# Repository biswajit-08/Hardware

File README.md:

# AC-DC Converter PCB

A custom AC-DC converter circuit and PCB designed using **KiCad**.

This project contains the complete schematic and PCB layout, including component placement, routing, and design files.

> ⚠️ **Safety Warning:** This project may involve hazardous mains voltage. Do not build, modify, test, or operate the circuit unless you understand electrical safety practices and have appropriate isolation, protection, equipment, and supervision.

---

## 📌 Project Overview

The objective of this project is to design a compact and organized PCB for an AC-DC power conversion circuit.

The project covers:

- Circuit schematic design
- Component selection
- PCB layout
- Component placement
- PCB routing
- Design-rule checking
- KiCad project management

---

## 🛠️ Design Software

| Tool | Purpose |
|---|---|
| KiCad | Schematic and PCB design |
| Git | Version control |
| GitHub | Project hosting and collaboration |

---

## 📁 Project Files

```text
AC-DC Converter/
│
├── AC-DC Converter.kicad_pro   # KiCad project
├── AC-DC Converter.kicad_sch   # Schematic
├── AC-DC Converter.kicad_pcb   # PCB layout
└── README.md                   # Project documentation
```

### KiCad Files

**`.kicad_pro`**

Contains the KiCad project configuration.

**`.kicad_sch`**

Contains the complete circuit schematic.

**`.kicad_pcb`**

Contains the PCB layout, including:

- Board outline
- Component footprints
- Component placement
- Copper tracks
- Routing
- PCB layers
- Design rules

---

## ⚡ Electrical Specifications

> Replace the values below with the actual specifications of your design.

| Parameter | Value |
|---|---|
| Input Voltage | TBD |
| Input Frequency | TBD |
| Output Voltage | TBD |
| Output Current | TBD |
| Output Power | TBD |
| Converter Topology | TBD |
| Isolation | TBD |
| PCB Layers | TBD |
| PCB Dimensions | TBD |

---

## 🔌 Functional Block Diagram

```text
        AC INPUT
           │
           ▼
   ┌─────────────────┐
   │ Input Protection│
   └────────┬────────┘
            │
            ▼
   ┌─────────────────┐
   │ Rectification   │
   └────────┬────────┘
            │
            ▼
   ┌─────────────────┐
   │ AC-DC Conversion│
   │ / Switching     │
   └────────┬────────┘
            │
            ▼
   ┌─────────────────┐
   │ Filtering       │
   └────────┬────────┘
            │
            ▼
        DC OUTPUT
```

> Update this block diagram to match the actual topology of your converter.

---

## 🧩 Main Components

The PCB contains the major components required for the converter, including:

- Input protection components
- Rectifier section
- Switching/conversion stage
- Transformer or isolation stage, if applicable
- Filtering components
- Voltage regulation/control circuitry
- Output terminals/connectors

The exact component values and part numbers are available in the KiCad schematic.

---

## 🎨 PCB Design

The PCB was designed with attention to:

- Component placement
- Signal routing
- Power routing
- Ground connections
- Clearance
- Track width
- Thermal considerations
- High-voltage and low-voltage separation

### PCB Design Stages

```text
Schematic
    │
    ▼
Component Selection
    │
    ▼
Footprint Assignment
    │
    ▼
PCB Placement
    │
    ▼
Routing
    │
    ▼
Design Rule Check
    │
    ▼
Fabrication
    │
    ▼
Assembly & Testing
```

---

## 🔍 Design Validation

Before fabrication, the design should be checked for:

- [ ] Electrical Rule Check (ERC)
- [ ] Design Rule Check (DRC)
- [ ] Unconnected nets
- [ ] Clearance violations
- [ ] Track-width requirements
- [ ] Component orientation
- [ ] Polarity of components
- [ ] Connector pinout
- [ ] Thermal requirements
- [ ] High-voltage clearance and creepage

---

## 🏭 Fabrication

Gerber and drill files can be generated from KiCad when the PCB is ready for manufacturing.

Recommended fabrication outputs:

```text
Fabrication/
├── Gerber files
├── Drill files
├── Board outline
├── Copper layers
├── Solder mask
├── Silkscreen
└── Fabrication drawings
```

---

## 🧪 Testing Plan

After fabrication and assembly, testing should be performed progressively.

### 1. Visual Inspection

Check:

- PCB damage
- Solder bridges
- Component orientation
- Incorrect component values
- Polarity
- Connector placement

### 2. Continuity Testing

Verify:

- No unintended short circuits
- Ground continuity
- Expected connections

### 3. Power-Up Testing

Use appropriate current limiting and isolation equipment.

Verify:

- Input behavior
- Output voltage
- Output ripple
- Temperature
- Current consumption
- Protection behavior

### 4. Load Testing

Test the converter with progressively increasing loads while monitoring:

- Output voltage
- Output current
- Temperature
- Efficiency
- Stability

---

## 📷 Project Images

Add PCB renders, schematic screenshots, and photographs here.

Example:

```text
images/
├── schematic.png
├── pcb-layout.png
├── pcb-3d-front.png
└── pcb-3d-back.png
```

Then display them using:

```markdown

```

---

## 📈 Future Improvements

Possible future improvements include:

- Improved thermal management
- Better PCB isolation
- Improved EMI/EMC performance
- Additional protection circuitry
- Status indicators
- Improved enclosure design
- Efficiency optimization
- Production-ready component selection
- Automated testing

---

## 📜 Version History

| Version | Description |
|---|---|
| v0.1 | Initial schematic and PCB design |
| v0.2 | PCB routing completed |
| v0.3 | Testing and validation |
| v1.0 | Final release |

---

## 👨‍💻 Author

**Biswajit Sahu**

Electrical & Electronics Engineering  
VSSUT, Burla

GitHub: [biswajit-08](https://github.com/biswajit-08)

---

## 📄 License

Choose an appropriate license before distributing the design commercially or for reuse.

---

## ⚠️ Disclaimer

This project is provided for educational and engineering purposes.

If the circuit interfaces with hazardous voltages, appropriate electrical safety procedures must be followed. The designer/user is responsible for validating the design, component ratings, PCB clearances, isolation, protection, and compliance requirements before applying power.

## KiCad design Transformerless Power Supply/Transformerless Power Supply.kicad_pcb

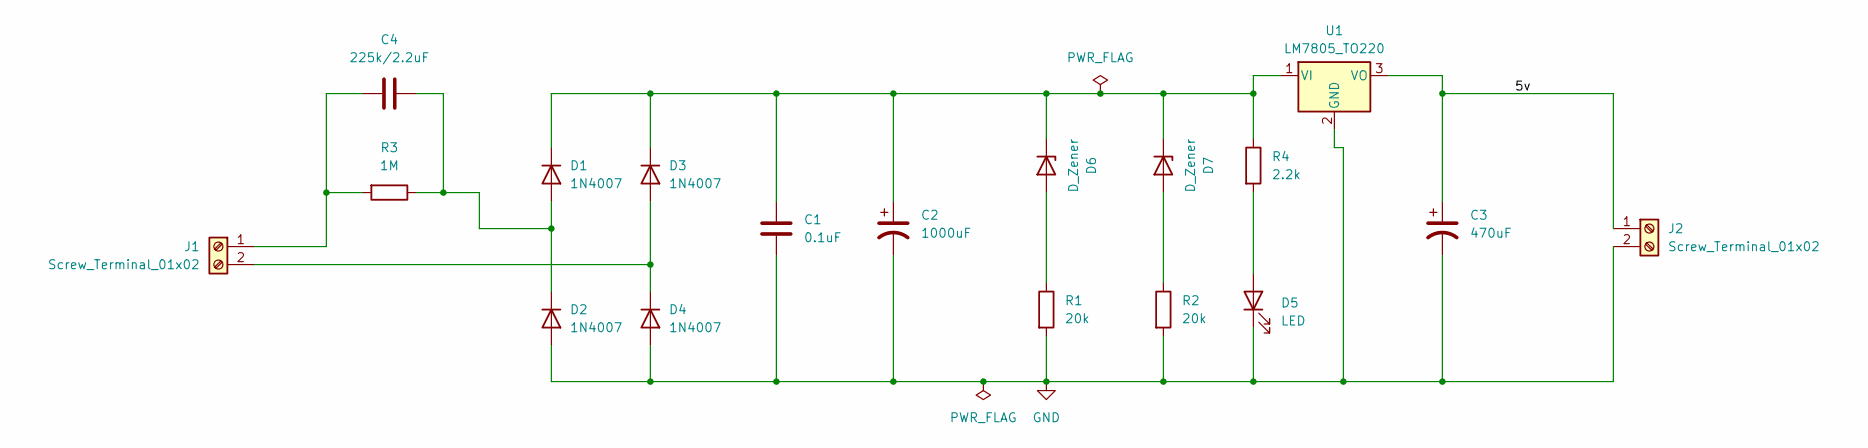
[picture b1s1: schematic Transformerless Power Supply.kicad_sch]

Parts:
C1: 0.1uF; C_Disc_D3.4mm_W2.1mm_P2.50mm
C2: 1000uF; CP_Radial_Tantal_D10.5mm_P5.00mm
C3: 470uF; CP_Radial_Tantal_D10.5mm_P5.00mm
C4: 225k/2.2uF; C_Rect_L18.0mm_W6.0mm_P15.00mm_FKS3_FKP3
D1, D2, D3, D4: 1N4007; D_DO-41_SOD81_P10.16mm_Horizontal
D5: LED; LED_D5.0mm
D6, D7: D_Zener; D_A-405_P7.62mm_Horizontal
J1, J2: Screw_Terminal_01x02; Wuerth_691311400102_P7.62mm
R1, R2: 20k; R_Axial_DIN0207_L6.3mm_D2.5mm_P7.62mm_Horizontal
R3: 1M; R_Axial_DIN0207_L6.3mm_D2.5mm_P7.62mm_Horizontal
R4: 2.2k; R_Axial_DIN0207_L6.3mm_D2.5mm_P7.62mm_Horizontal
U1: LM7805_TO220; TO-220-3_Vertical

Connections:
/5v: C3.1, J2.1, U1.3 (VO)
GND: C1.2, C2.2, C3.2, D2.2 (A), D4.2 (A), D5.1 (K), J2.2, R1.2, R2.2, U1.2 (GND)
unnamed: C4.1, D1.2 (A), D2.1 (K), R3.1
unnamed: C1.1, C2.1, D1.1 (K), D3.1 (K), D6.1 (K), D7.1 (K), R4.1, U1.1 (VI)
unnamed: D3.2 (A), D4.1 (K), J1.2
unnamed: D5.2 (A), R4.2
unnamed: D6.2 (A), R1.1
unnamed: D7.2 (A), R2.1
unnamed: C4.2, J1.1, R3.2

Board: 2 copper layers, 18 parts (0 on the bottom side), 9 nets, no tracks yet.

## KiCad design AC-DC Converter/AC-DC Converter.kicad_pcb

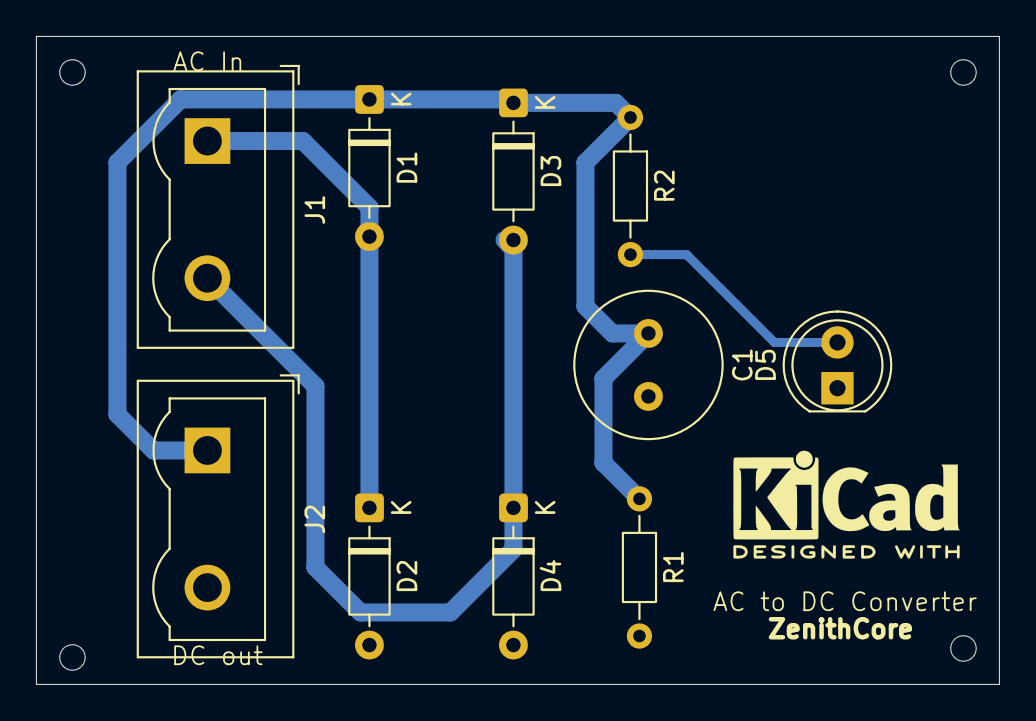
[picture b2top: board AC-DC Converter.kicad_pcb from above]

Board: 2 copper layers, 53.5 x 36.0 mm, 10 parts (0 on the bottom side), 5 nets.

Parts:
C1: 1000uF; C_Radial_D8.0mm_H11.5mm_P3.50mm
D1, D2, D3, D4: D; D_DO-35_SOD27_P7.62mm_Horizontal
D5: LED; LED_D5.0mm
J1, J2: Screw_Terminal_01x02; Wuerth_691311400102_P7.62mm
R1: 10K; R_Axial_DIN0204_L3.6mm_D1.6mm_P7.62mm_Horizontal
R2: 2.2K; R_Axial_DIN0204_L3.6mm_D1.6mm_P7.62mm_Horizontal

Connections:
GND: C1.2, D2.2 (A), D4.2 (A), D5.1 (K), J2.2, R1.2
unnamed: D1.2 (A), D2.1 (K), J1.2 (Pin_1_1)
unnamed: C1.1, D1.1 (K), D3.1 (K), J2.1, R1.1, R2.1
unnamed: D3.2 (A), D4.1 (K), J1.1 (Pin_2_2)
unnamed: D5.2 (A), R2.2
